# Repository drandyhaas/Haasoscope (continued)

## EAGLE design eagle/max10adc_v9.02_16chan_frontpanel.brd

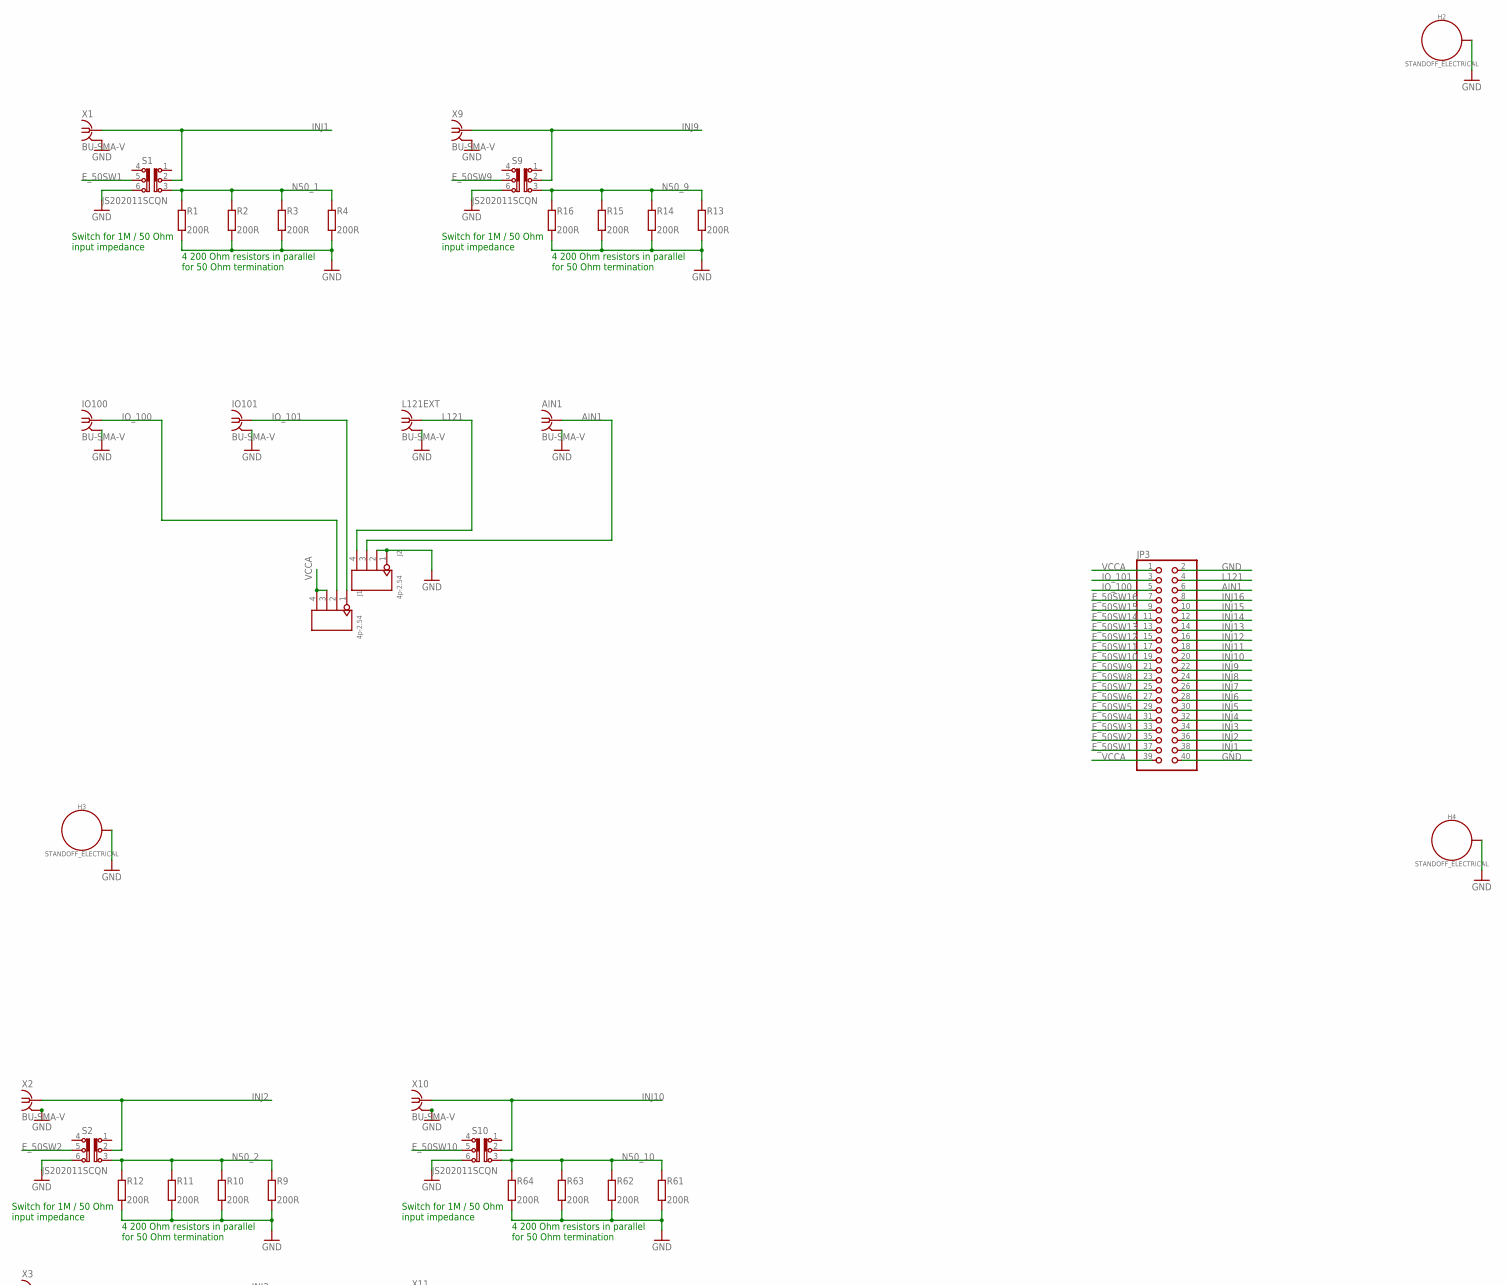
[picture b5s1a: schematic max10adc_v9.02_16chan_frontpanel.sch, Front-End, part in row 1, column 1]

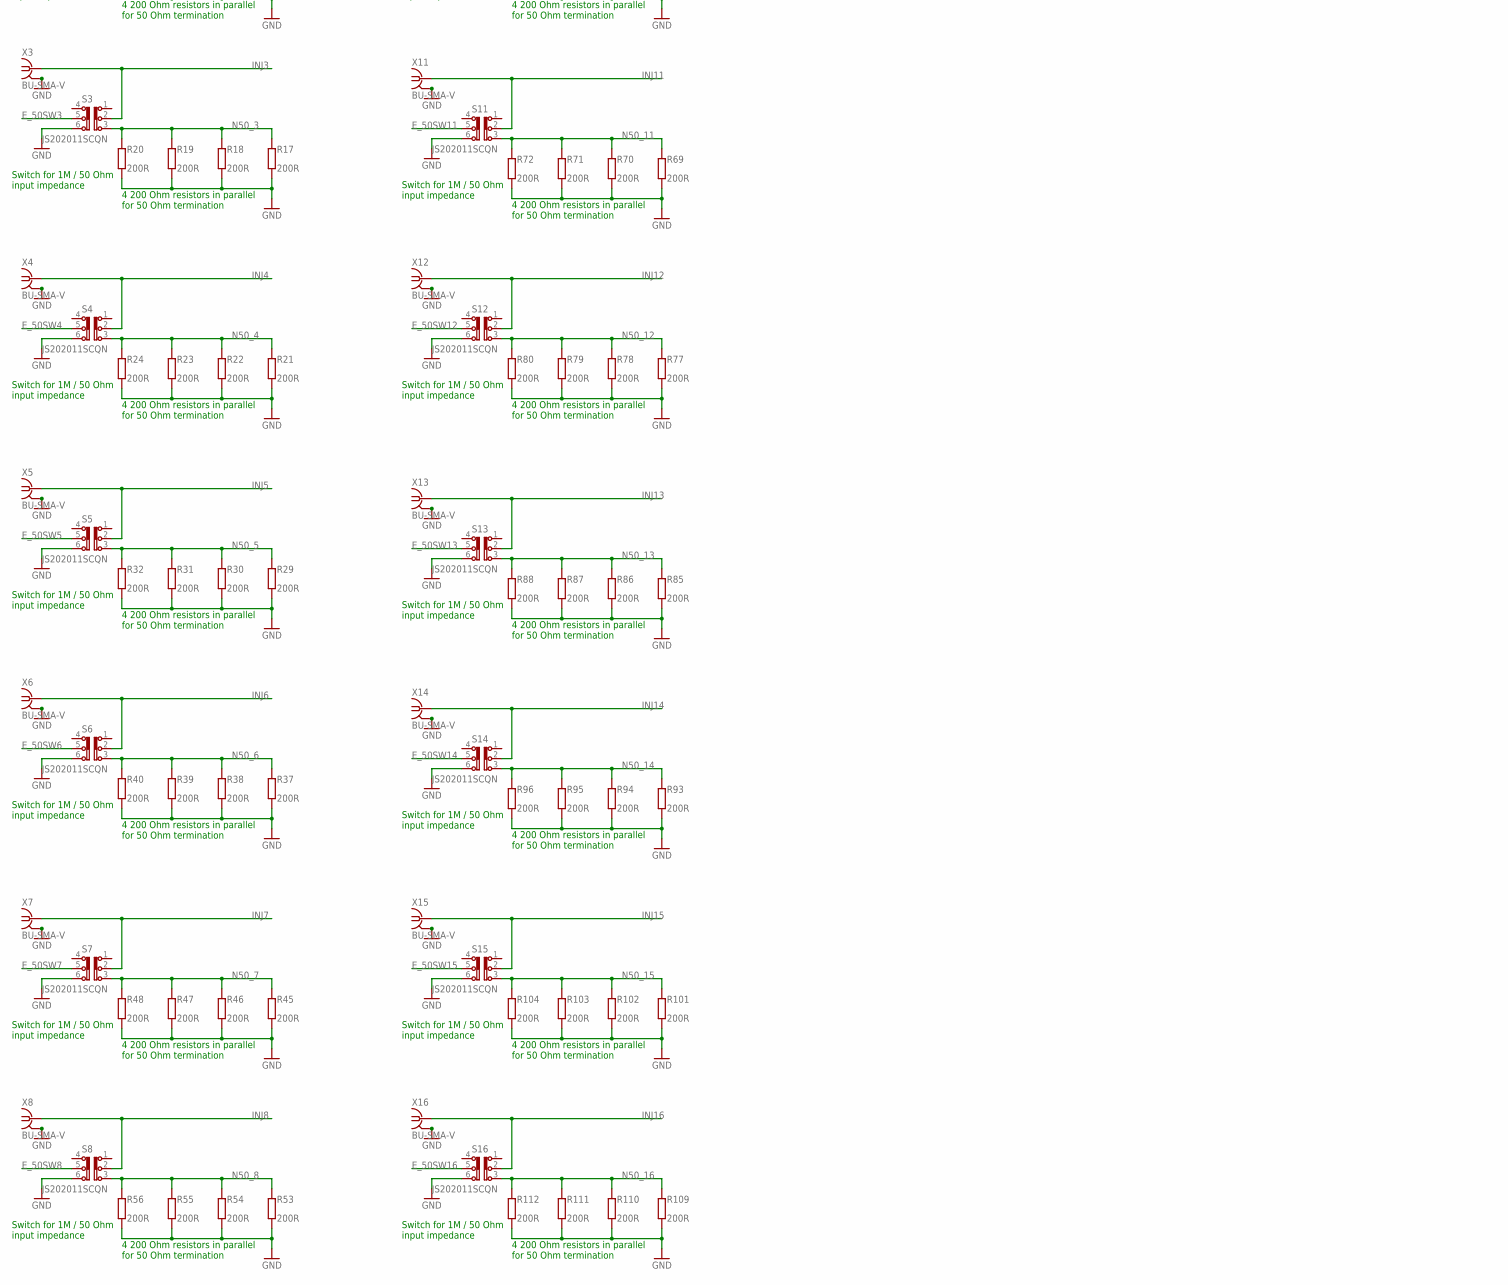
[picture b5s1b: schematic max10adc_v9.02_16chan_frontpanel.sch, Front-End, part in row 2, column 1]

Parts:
AIN1: BU-SMA-V
H2, H3, H4: STANDOFF_ELECTRICAL; STANDOFF-ELECTRICAL
IO100, IO101: BU-SMA-V
J1, J2: 4p-2.54; H4-2.54
JP3: PINHD-2X20; 2X20
L121EXT: BU-SMA-V
R1, R2, R3, R4, R9, R10, R11, R12, R13, R14, R15, R16, R17, R18, R19, R20, R21, R22, R23, R24, R29, R30, R31, R32, R37, R38, R39, R40, R45, R46, R47, R48, R53, R54, R55, R56, R61, R62, R63, R64, R69, R70, R71, R72, R77, R78, R79, R80, R85, R86, R87, R88, R93, R94, R95, R96, R101, R102, R103, R104, R109, R110, R111, R112: 200R; R0805
S1, S2, S3, S4, S5, S6, S7, S8, S9, S10, S11, S12, S13, S14, S15, S16: JS202011SCQN
X1, X2, X3, X4, X5, X6, X7, X8, X9, X10, X11, X12, X13, X14, X15, X16: BU-SMA-V

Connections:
AIN1: AIN1.1, J2.3, JP3.6
E_50SW1: JP3.37, S1.5
E_50SW2: JP3.35, S2.5
E_50SW3: JP3.33, S3.5
E_50SW4: JP3.31, S4.5
E_50SW5: JP3.29, S5.5
E_50SW6: JP3.27, S6.5
E_50SW7: JP3.25, S7.5
E_50SW8: JP3.23, S8.5
E_50SW9: JP3.21, S9.5
E_50SW10: JP3.19, S10.5
E_50SW11: JP3.17, S11.5
E_50SW12: JP3.15, S12.5
E_50SW13: JP3.13, S13.5
E_50SW14: JP3.11, S14.5
E_50SW15: JP3.9, S15.5
E_50SW16: JP3.7, S16.5
GND: AIN1.2, AIN1.3 (2), AIN1.4 (2), AIN1.5 (2), H2.P1, H3.P1, H4.P1, IO100.2, IO100.3 (2), IO100.4 (2), IO100.5 (2), IO101.2, IO101.3 (2), IO101.4 (2), IO101.5 (2), J2.1, J2.2, JP3.2, JP3.40, L121EXT.2, L121EXT.3 (2), L121EXT.4 (2), L121EXT.5 (2), R1.2, R2.2, R3.2, R4.2, R9.2, R10.2, R11.2, R12.2, R13.2, R14.2, R15.2, R16.2, R17.2, R18.2, R19.2, R20.2, R21.2, R22.2, R23.2, R24.2, R29.2, R30.2, R31.2, R32.2, R37.2, R38.2, R39.2, R40.2, R45.2, R46.2, R47.2, R48.2, R53.2, R54.2, R55.2, R56.2, R61.2, R62.2, R63.2, R64.2, R69.2, R70.2, R71.2, R72.2, R77.2, R78.2, R79.2, R80.2, R85.2, R86.2, R87.2, R88.2, R93.2, R94.2, R95.2, R96.2, R101.2, R102.2, R103.2, R104.2, R109.2, R110.2, R111.2, R112.2, S1.6, S2.6, S3.6, S4.6, S5.6, S6.6, S7.6, S8.6, S9.6, S10.6, S11.6, S12.6, S13.6, S14.6, S15.6, S16.6, X1.2, X1.3 (2), X1.4 (2), X1.5 (2), X2.2, X2.3 (2), X2.4 (2), X2.5 (2), X3.2, X3.3 (2), X3.4 (2), X3.5 (2), X4.2, X4.3 (2), X4.4 (2), X4.5 (2), X5.2, X5.3 (2), X5.4 (2), X5.5 (2), X6.2, X6.3 (2), X6.4 (2), X6.5 (2), X7.2, X7.3 (2), X7.4 (2), X7.5 (2), X8.2, X8.3 (2), X8.4 (2), X8.5 (2), X9.2, X9.3 (2), X9.4 (2), X9.5 (2), X10.2, X10.3 (2), X10.4 (2), X10.5 (2), X11.2, X11.3 (2), X11.4 (2), X11.5 (2), X12.2, X12.3 (2), X12.4 (2), X12.5 (2), X13.2, X13.3 (2), X13.4 (2), X13.5 (2), X14.2, X14.3 (2), X14.4 (2), X14.5 (2), X15.2, X15.3 (2), X15.4 (2), X15.5 (2), X16.2, X16.3 (2), X16.4 (2), X16.5 (2)
INJ1: JP3.38, S1.2, X1.1
INJ2: JP3.36, S2.2, X2.1
INJ3: JP3.34, S3.2, X3.1
INJ4: JP3.32, S4.2, X4.1
INJ5: JP3.30, S5.2, X5.1
INJ6: JP3.28, S6.2, X6.1
INJ7: JP3.26, S7.2, X7.1
INJ8: JP3.24, S8.2, X8.1
INJ9: JP3.22, S9.2, X9.1
INJ10: JP3.20, S10.2, X10.1
INJ11: JP3.18, S11.2, X11.1
INJ12: JP3.16, S12.2, X12.1
INJ13: JP3.14, S13.2, X13.1
INJ14: JP3.12, S14.2, X14.1
INJ15: JP3.10, S15.2, X15.1
INJ16: JP3.8, S16.2, X16.1
IO_100: IO100.1, J1.2, JP3.5
IO_101: IO101.1, J1.1, JP3.3
L121: J2.4, JP3.4, L121EXT.1
N50_1: R1.1, R2.1, R3.1, R4.1, S1.3
N50_2: R9.1, R10.1, R11.1, R12.1, S2.3
N50_3: R17.1, R18.1, R19.1, R20.1, S3.3
N50_4: R21.1, R22.1, R23.1, R24.1, S4.3
N50_5: R29.1, R30.1, R31.1, R32.1, S5.3
N50_6: R37.1, R38.1, R39.1, R40.1, S6.3
N50_7: R45.1, R46.1, R47.1, R48.1, S7.3
N50_8: R53.1, R54.1, R55.1, R56.1, S8.3
N50_9: R13.1, R14.1, R15.1, R16.1, S9.3
N50_10: R61.1, R62.1, R63.1, R64.1, S10.3
N50_11: R69.1, R70.1, R71.1, R72.1, S11.3
N50_12: R77.1, R78.1, R79.1, R80.1, S12.3
N50_13: R85.1, R86.1, R87.1, R88.1, S13.3
N50_14: R93.1, R94.1, R95.1, R96.1, S14.3
N50_15: R101.1, R102.1, R103.1, R104.1, S15.3
N50_16: R109.1, R110.1, R111.1, R112.1, S16.3
VCCA: J1.3, J1.4, JP3.1, JP3.39

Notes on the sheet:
4 200 Ohm resistors in parallel for 50 Ohm termination
Switch for 1M / 50 Ohm input impedance

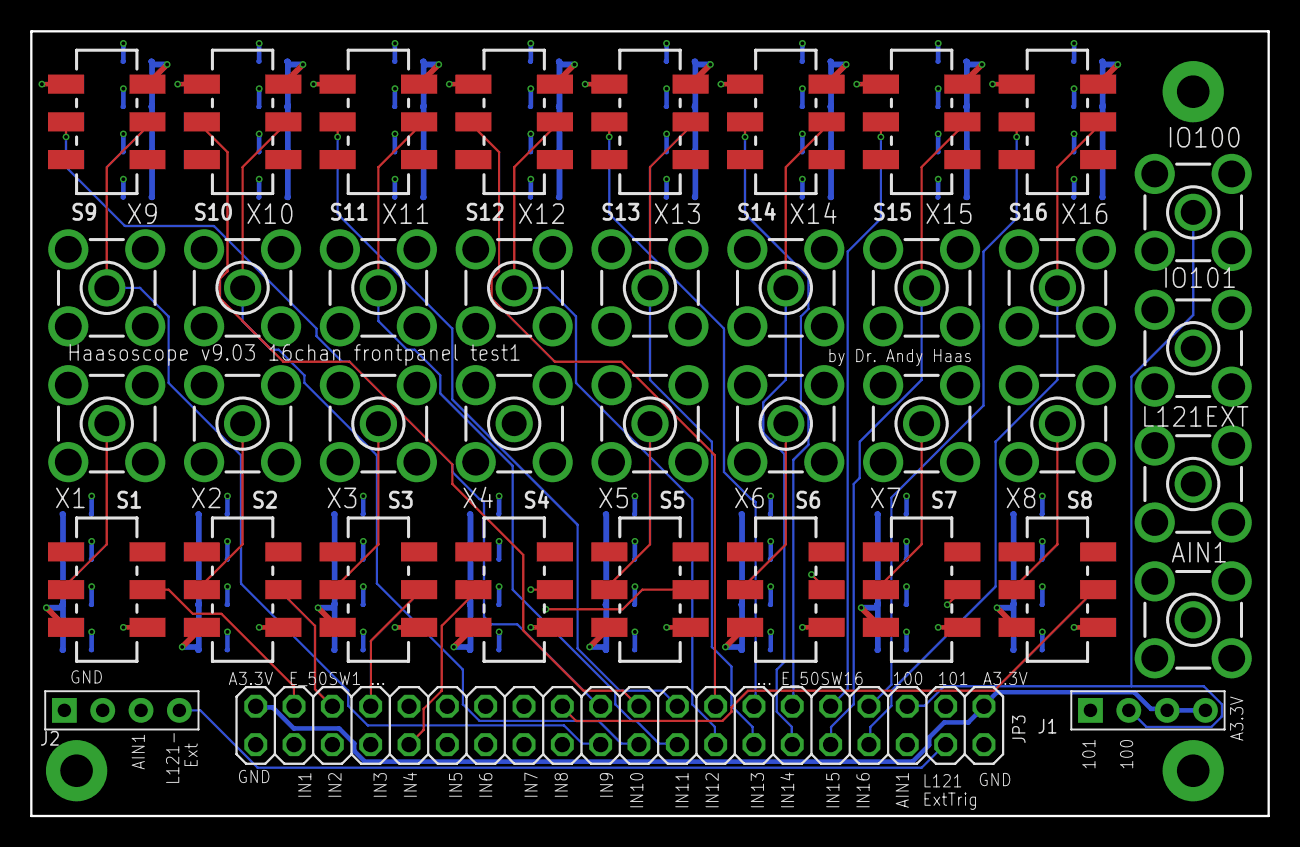
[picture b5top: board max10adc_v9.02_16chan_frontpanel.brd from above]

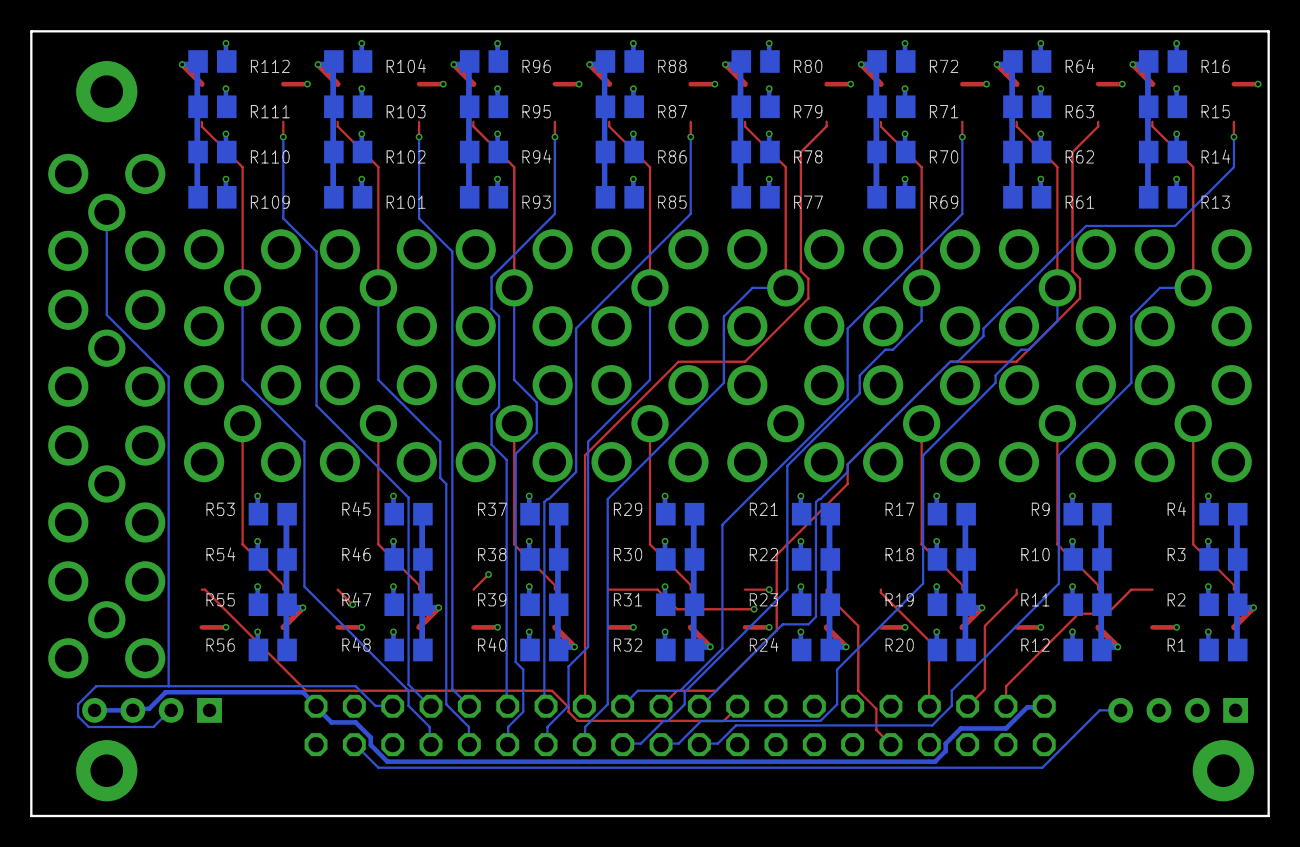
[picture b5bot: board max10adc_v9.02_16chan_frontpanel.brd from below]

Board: 4 copper layers, 82.0 x 52.0 mm, 106 parts (64 on the bottom side), 54 nets.

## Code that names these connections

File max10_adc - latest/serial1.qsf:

# -------------------------------------------------------------------------- #
#
# Copyright (C) 1991-2013 Altera Corporation
# Your use of Altera Corporation's design tools, logic functions 
# and other software and tools, and its AMPP partner logic 
# functions, and any output files from any of the foregoing 
# (including device programming or simulation files), and any 
# associated documentation or information are expressly subject 
# to the terms and conditions of the Altera Program License 
# Subscription Agreement, Altera MegaCore Function License 
# Agreement, or other applicable license agreement, including, 
# without limitation, that your use is for the sole purpose of 
# programming logic devices manufactured by Altera and sold by 
# Altera or its authorized distributors.  Please refer to the 
# applicable agreement for further details.
#
# -------------------------------------------------------------------------- #
#
# Quartus II 32-bit
# Version 13.0.1 Build 232 06/12/2013 Service Pack 1 SJ Web Edition
# Date created = 17:22:48  September 13, 2016
#
# -------------------------------------------------------------------------- #
#
# Notes:
#
# 1) The default values for assignments are stored in the file:
#		serial1_assignment_defaults.qdf
#    If this file doesn't exist, see file:
#		assignment_defaults.qdf
#
# 2) Altera recommends that you do not modify this file. This
#    file is updated automatically by the Quartus II software
#    and any changes you make may be lost or overwritten.
#
# -------------------------------------------------------------------------- #


set_global_assignment -name FAMILY "MAX 10"
set_global_assignment -name DEVICE 10M08SAE144C8GES
set_global_assignment -name TOP_LEVEL_ENTITY serial1
set_global_assignment -name ORIGINAL_QUARTUS_VERSION "13.0 SP1"
set_global_assignment -name PROJECT_CREATION_TIME_DATE "17:22:48  SEPTEMBER 13, 2016"
set_global_assignment -name LAST_QUARTUS_VERSION 15.0.0
set_global_assignment -name PROJECT_OUTPUT_DIRECTORY output_files
set_global_assignment -name MIN_CORE_JUNCTION_TEMP 0
set_global_assignment -name MAX_CORE_JUNCTION_TEMP 85
set_global_assignment -name ERROR_CHECK_FREQUENCY_DIVISOR 2
set_global_assignment -name PARTITION_NETLIST_TYPE SOURCE -section_id Top
set_global_assignment -name PARTITION_FITTER_PRESERVATION_LEVEL PLACEMENT_AND_ROUTING -section_id Top
set_global_assignment -name PARTITION_COLOR 16764057 -section_id Top
set_global_assignment -name STRATIX_DEVICE_IO_STANDARD "3.3-V LVTTL"
set_location_assignment PIN_93 -to 232_in
set_location_assignment PIN_92 -to 232_out
set_location_assignment PIN_33 -to clk_flash_out
set_location_assignment PIN_38 -to din1[7]
set_location_assignment PIN_39 -to din1[6]
set_location_assignment PIN_41 -to din1[5]
set_location_assignment PIN_43 -to din1[4]
set_location_assignment PIN_44 -to din1[3]
set_location_assignment PIN_45 -to din1[2]
set_location_assignment PIN_46 -to din1[1]
set_location_assignment PIN_47 -to din1[0]
set_location_assignment PIN_50 -to din2[7]
set_location_assignment PIN_52 -to din2[6]
set_location_assignment PIN_54 -to din2[5]
set_location_assignment PIN_55 -to din2[4]
set_location_assignment PIN_56 -to din2[3]
set_location_assignment PIN_57 -to din2[2]
set_location_assignment PIN_58 -to din2[1]
set_location_assignment PIN_59 -to din2[0]
set_location_assignment PIN_60 -to din3[7]
set_location_assignment PIN_62 -to din3[6]
set_location_assignment PIN_64 -to din3[5]
set_location_assignment PIN_65 -to din3[4]
set_location_assignment PIN_66 -to din3[3]
set_location_assignment PIN_69 -to din3[2]
set_location_assignment PIN_70 -to din3[1]
set_location_assignment PIN_74 -to din3[0]
set_location_assignment PIN_75 -to din4[7]
set_location_assignment PIN_76 -to din4[6]
set_location_assignment PIN_77 -to din4[5]
set_location_assignment PIN_78 -to din4[4]
set_location_assignment PIN_79 -to din4[3]
set_location_assignment PIN_81 -to din4[2]
set_location_assignment PIN_84 -to din4[1]
set_location_assignment PIN_85 -to din4[0]
set_location_assignment PIN_96 -to 232_out2
set_location_assignment PIN_120 -to led1
set_location_assignment PIN_121 -to led2
set_location_assignment PIN_124 -to led3
set_location_assignment PIN_28 -to outclk_pin
set_location_assignment PIN_86 -to trig_in_towards_left
set_location_assignment PIN_87 -to trig_out_to_right
set_location_assignment PIN_106 -to trig_out_to_left
set_location_assignment PIN_105 -to trig_in_towards_right
set_global_assignment -name PROJECT_IP_REGENERATION_POLICY ALWAYS_REGENERATE_IP
set_global_assignment -name POWER_PRESET_COOLING_SOLUTION "23 MM HEAT SINK WITH 200 LFPM AIRFLOW"
set_global_assignment -name POWER_BOARD_THERMAL_MODEL "NONE (CONSERVATIVE)"
set_global_assignment -name FLOW_ENABLE_POWER_ANALYZER ON
set_global_assignment -name POWER_DEFAULT_INPUT_IO_TOGGLE_RATE "12.5 %"
set_location_assignment PIN_27 -to clock_ext_osc
set_location_assignment PIN_26 -to clock_in
set_location_assignment PIN_131 -to CD
set_location_assignment PIN_140 -to CLKO
set_location_assignment PIN_132 -to CS
set_location_assignment PIN_135 -to DO
set_location_assignment PIN_134 -to RSTO
set_parameter -name SERIAL_BAUD_RATE 1500000
set_parameter -name SERIAL_BAUD_RATE_ARDUINO 9600
set_location_assignment PIN_22 -to outsel_out
set_location_assignment PIN_25 -to format_out
set_location_assignment PIN_24 -to div_out
set_global_assignment -name EDA_SIMULATION_TOOL "ModelSim-Altera (Verilog)"
set_global_assignment -name EDA_TIME_SCALE "1 ps" -section_id eda_simulation
set_global_assignment -name EDA_OUTPUT_DATA_FORMAT "VERILOG HDL" -section_id eda_simulation
set_global_assignment -name EDA_USER_COMPILED_SIMULATION_LIBRARY_DIRECTORY "C:\\haas\\Dropbox\\documents\\FPGA\\QuartusII\\serial_vga_pong_max10_adc\\simulation\\modelsim" -section_id eda_simulation
set_global_assignment -name EDA_GENERATE_FUNCTIONAL_NETLIST ON -section_id eda_simulation
set_location_assignment PIN_110 -to carryin -disable
set_location_assignment PIN_111 -to carryout -disable
set_location_assignment PIN_130 -to ledbase
set_location_assignment PIN_98 -to 232_in2
set_location_assignment PIN_88 -to offset[0]
set_location_assignment PIN_89 -to offset[1]
set_location_assignment PIN_90 -to offset[2]
set_location_assignment PIN_91 -to offset[3]
set_location_assignment PIN_21 -to gainsw[0]
set_location_assignment PIN_29 -to gainsw[1]
set_location_assignment PIN_100 -to gainsw[2]
set_location_assignment PIN_101 -to gainsw[3]
set_parameter -name ADC_RAM_WIDTH 12
set_location_assignment PIN_127 -to led4
set_location_assignment PIN_32 -to clk_flash_out_2
set_global_assignment -name BDF_FILE serial1.bdf
set_global_assignment -name VERILOG_FILE ring_counter.v
set_global_assignment -name VERILOG_FILE tdc2.v
set_global_assignment -name VERILOG_FILE oscillo.v
set_global_assignment -name VERILOG_FILE serialprocessor.v
set_global_assignment -name VERILOG_FILE serialprocessor_slave.v
set_global_assignment -name VHDL_FILE SSD1306.vhd
set_global_assignment -name VHDL_FILE SPI.vhd
set_global_assignment -name VHDL_FILE i2c_master.vhd
set_global_assignment -name VERILOG_FILE async.v
set_global_assignment -name VERILOG_FILE demux1.v
set_global_assignment -name CDF_FILE output_files/Chain1.cdf
set_global_assignment -name CDF_FILE output_files/Chain2.cdf
set_global_assignment -name QIP_FILE mypll2.qip
set_global_assignment -name QIP_FILE ram1.qip
set_global_assignment -name QIP_FILE dpram2.qip
set_global_assignment -name QIP_FILE lp_ram_dp.qip
set_global_assignment -name QIP_FILE myadc/synthesis/myadc.qip
set_location_assignment PIN_118 -to i2c_sda
set_location_assignment PIN_119 -to i2c_scl
set_location_assignment PIN_110 -to usb_dataio[0] -disable
set_location_assignment PIN_111 -to usb_dataio[1] -disable
set_location_assignment PIN_113 -to usb_dataio[2] -disable
set_location_assignment PIN_114 -to usb_dataio[3] -disable
set_location_assignment PIN_118 -to usb_dataio[4] -disable
set_location_assignment PIN_119 -to usb_dataio[5] -disable
set_location_assignment PIN_122 -to usb_dataio[6] -disable
set_location_assignment PIN_132 -to usb_dataio[7] -disable
set_location_assignment PIN_134 -to usb_wr -disable
set_location_assignment PIN_135 -to usb_txe_busy -disable
set_location_assignment PIN_140 -to usb_clk60 -disable
set_instance_assignment -name PARTITION_HIERARCHY root_partition -to | -section_id Top

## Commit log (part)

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2018-10-29 acquire only samplestosend samples, and only signal data ready after all samples have been acquired
2018-10-30 reset highres counter after trigger to prevent glitches
2018-10-30 read the firmware version
2018-10-30 respond with the firmware version to command 147
2018-10-30 change rising edge trigger message to falling
2018-10-31 for no BSOD
2018-11-01 update some parts to TTI
2018-11-02 formatting
2018-11-19 for board v9.0
2018-11-26 remove v8 v9 separate files
2018-11-26 remove v8 stuff
2018-11-26 read v9 switches
2018-11-26 set gain to 1.1 for v9.0 boards
2018-11-27 for 9.01
2018-11-27 for allpcb
2018-12-04 just 6miil distance between drills and traces
2018-12-04 better routing, using just 6mil distance between drills and traces
2018-12-04 150 Ohm inputs for v9.0 boards?
2018-12-07 300 Ohm termination
2018-12-12 removed because not used
2018-12-15 Update README.md
    I've created a 3D model for bottom case. It might come handy also for others.
2018-12-19 case for v8.81
2018-12-22 names on silkscreen
2018-12-22 bottom labels
2019-01-07 v9.01 calib
2019-01-09 minimal serial test
2019-01-10 9.01 calib
2019-01-28 fix crash in printout
2019-01-29 optionally save chan 0 to file
2019-01-30 version 16, dont output clk50 if youre the last one, to reduce noise
2019-02-04 savetofile placement
2019-02-05 check for raspberry pi
2019-02-05 serialdelaytimerwait defaults
2019-02-06 i2c comment
2019-02-16 HW_INIT: Same content, different structure of data
2019-03-21 Show calculated frequency of the signal
2019-03-21 for stacking
2019-03-29 select backend better
2019-04-15 slower on aarch
2019-04-15 linux driver
2019-04-15 linux driver header for rk-3328
2019-04-16 Fixed gaps between base and side walls
2019-05-10 Converted to Python 3.5 but doesn't work.
2019-05-10 Add some debugs.
2019-05-10 theboard forced as int.
2019-05-10 Working version.
2019-05-10 Fix getfirmwareversion function.
2019-05-10 Fix function tellsamplessend.
2019-05-10 Fix function tellbytesskip.
2019-05-10 Fix function telldownsample.
2019-05-10 Fix function settriggertime.
2019-05-10 Fix function tellserialdelaytimerwait.
2019-05-10 Fix function tellSPIsetup.
2019-05-10 Fix function tellrolltrig.
2019-05-10 Fix function settriggerpoint.
2019-05-10 Fix function telllockinnumtoshift.
2019-05-11 Fix function telltickstowait.
2019-05-11 Fix trigger related functions.
    tellminidisplaychan
    settriggerthresh
    settriggerthresh2
    settriggertype
2019-05-11 Fix function writefirmchan.
2019-05-11 Fix function toggleautorearm.
2019-05-11 Fix function getIDs.
2019-05-11 Fix functions setbacktoserialreadout getotherdata.
2019-05-11 Fix functions getmax10adc getdata.
2019-05-11 Fix functions init getswitchdata getchannels.
2019-05-11 Remove init_test.
2019-05-11 Remove trailing spaces.
2019-05-11 Set savetofile to false.
2019-05-11 Add .gitignore for Python.
2019-07-24 show TDC read
2019-11-20 working on 16 chan board
2019-11-22 2.5msps and 12 bit ram for one channel
2019-12-03 for chan 3 12 bit 2.5Msps
2019-12-03 4x less gain and associated compensation, and input 6 pin connector
2019-12-05 with BOM
2019-12-06 MAX11105
2019-12-09 with 24pF fixed caps
2019-12-10 12 bit trigger and highres
2019-12-12 front panel with 50 Ohm termination and SMAs
2019-12-17 back connectors
2019-12-17 no old drawing
2019-12-17 working OK to 0th order
2019-12-17 trigger stuff working
2019-12-18 initial qt gui
2019-12-18 just do new gui in head branch
2019-12-18 more functionality
2019-12-19 select channels and trigging on channels
2019-12-19 more scrolling, keys, etc
2019-12-20 oversampling
2019-12-20 trigger points
2019-12-27 qwheelevent fix?
2019-12-27 record to file in menu
2020-01-06 oops, remove debug message
2020-01-06 xscaling in file
2020-06-10 test for python3
2020-06-10 some fixes
2020-06-12 a few more bugs
2020-07-05 quit when serial fails
2020-09-08 multi board bug fixes
2020-11-04 Initial check-in of Dockerfile to run Haasoscope in a container.
2020-11-10 for xhost
2020-11-10 command line options
2021-04-16 options for serialdelaytimerwait and numboard
2021-04-16 save data for other board channels too
2021-04-16 find usb connections
2021-04-16 for connecting multiple v9 boards
2021-04-16 connecting case
2021-04-19 for python3
2021-04-19 need baud rate for USB2 in python3
2021-04-19 formatting warnings fixes
2021-04-22 150 ohm termination
2021-04-23 ripyl
2021-04-25 prepare to merge version9
2021-04-25 getting ready for trigout instead of analog in
2021-04-25 trigout pins 6 7 8 10 instead of any analog in
2021-04-26 try to support more than 10 boards
2021-04-26 firmware 18, more than 10 boards
2021-04-26 supporting more than 10 boards, requiring firmware 17 or higher
2021-04-27 for more than 10
2021-04-27 trigger recovery test
2021-04-28 send out trigger syncing info to delaycounter
2021-04-29 for sending triggers and clock out
2021-05-01 wait for normal triggers to stop before calibrating trigger bins
2021-05-02 adjustable clock phase, for sending triggers
2021-05-03 store all digital logic analyzer bits from all boards
2021-05-04 talk to trigger board over serial
2021-05-05 be careful to send out test triggers using the same timing as the real triggers
2021-05-05 rename t
2021-05-05 increment clock phase by 3ns after sync loss
2021-05-05 swap spare left and right, send out just one trigger firing
2021-05-06 h5py file writing
2021-05-06 all boards send triggers out to the right when in noselftrig mode
2021-05-06 some minor options
2021-05-08 set seed on trigboard
2021-05-08 prescale integer
2021-05-08 no trigboard by default
2021-05-08 persist
2021-05-08 early persist plot
2021-05-09 persist plot minor
2021-05-09 put back slow adc
2021-05-09 can turn off display of slow adc channels
2021-05-10 make sure we can talk to the trig board
2021-05-12 for prescale on trigboard
2021-05-13 minor, and expect all boards to have a trigger cable connection
2021-05-13 for rolling control of trigboard
2021-05-18 fastusb2
2021-05-18 usb slow working
2021-05-18 basically working
2021-05-19 faster
2021-05-19 exceptions, and no parallel
2021-05-19 few more speedups, now 500 Hz for r12 for b3
2021-05-19 pwrsv line
2021-05-19 handle negative y values, print MB/s
2021-05-20 3U rack compatible
2021-05-21 3U rack backplane
2021-05-21 before routing
2021-05-21 just look for Haasoscope in ftdi name
2021-05-22 add sdc for timing checks
2021-05-22 almost passes timing
2021-05-23 Fix downsample
2021-05-23 Hold timing exception
2021-05-23 comment out the split between usb60 and other clocks in the sdc file, since it caused occasional issues with ch0 readout!
2021-05-24 fixed the glitch in the first sample of ch0, and pass timing, though with a few set_false_paths
2021-05-24 get rid of set_false_paths for dp_ram - we fail timing, but the firmware works
2021-05-25 markers
2021-05-26 working pretty well, but r12 is missing a sample, and first 2 points of ch0 are identical
2021-05-26 working well, but first 2 points of ch0 are identical
2021-05-27 add ram_width 13
2021-05-27 working on timing and ch123 in nsmp mode
2021-05-28 Working for all channels, by padding start of each channel by 1 byte and then accounting for it in software
2021-05-28 Working well on all Nsamples, with readout on all channels aligned to trigger the same as non-usb2
2021-05-28 Don't bother checking for switch changes if we're not drawing
2021-05-28 update IP
2021-05-28 work on timing a little
2021-05-30 count SendCount_fast down to 0, for faster comparison set usb60 clock asynchronous in sdc again passing timing for setup and hold firmware v19
2021-05-30 remove uniqueid false path
2021-05-31 use clk_50 from pll output set input output delays and pass timing and constrain all paths
2021-06-01 nbytes
2021-06-01 working well accounted for rdaddress latency
2021-06-02 better check for fastusb devices
2021-06-02 add ftdi_config.sh
2021-06-02 fix spacing of trigboard
2021-06-02 add 6mm on top and bottom, to fit in sliders
2021-06-02 lower timeouts on fastusb during mapping
2021-06-03 lower timeouts on fastusb during mapping for real, and set max adc read to 32 bytes
2021-06-03 fix averaging
2021-06-03 fix oversampling average and rms for oversampling
2021-06-03 serialdelaytimer for max10adc sending can set slow adc channels on command line
2021-06-07 set output clock to pllin
2021-06-07 flying fast option
2021-06-07 comments on 51-rules
2021-06-08 faster logic analyzer readout
2021-06-08 don't auto rearm in fastusb mode
2021-06-09 reset stuff during firmware read
2021-06-10 mt compatible things
2021-06-10 mt switchable
2021-06-10 mt command line argument and clean up other arguments
2021-06-10 put usb serial on bottom clean up wire stubs
2021-06-10 output clk don't reset
2021-06-13 pylibftdi and pyftdi reading, for non-mt at least
2021-06-13 pyftdi reading with mt
2021-06-13 pyftdi reading with mt and logicanalyzer and do purgebuffer just for ftd2xx, for now
2021-06-13 adjust chunksize for logicanalyzer
2021-06-14 minor, less printouts, etc.
2021-06-14 minor, settings for ftdi etc.
2021-06-14 auto trigboard port
2021-06-14 run trig board at 921600 baud
2021-06-15 remove 2 wire stubs
2021-06-22 specify data types for h5py writing
2021-07-06 add gnd layer on layer 15
2021-07-07 routed v9.10 6layer rack
2021-09-14 add serial decode for UART in Qt
2021-09-15 set ripyl false
2021-09-20 set font size to 11 pixels, and have toggle for allowing same channel coincidence, firmware v21
2021-09-30 fix file status bar message
2021-09-30 example h5py file reading
2021-09-30 save in float32, so time axis has enough precision (and voltage?)
2021-11-23 ignore tty USB2 connections when doing fastusb2
2021-11-23 print error and exit if you try to do fastusb with old firmware
2022-03-02 read out the number of triggers seen, gettrigratecounter
2022-03-03 get trigratecounter every 10s and print to chantext area allow cointime to also be "deadtime" for trigger rate counter
2022-03-07 final touches on trigger rate, firmware 22
2022-03-07 slow paths for trigger counter
2022-05-17 Display trigger threshold
2022-05-26 resend rolling command
2022-05-26 trigger counter every 2s, printouts for rolling trigger
2022-05-26 10 MHz clk on pin 100 (debug4) 1 kHz pulse (SP) on pin 89 (debug1) 50 Hz readout pulse on pin 90 (debug2)
2022-07-06 Initial attempt, need to add duplicate memory buffers
2022-07-20 Initial changes to oscillo.v to include Trigger as an out pin on 106
2022-07-21 averaging machinery in place, works on fastusb2
2022-07-23 100 averages, 1 cycle sort of right, but too much rounding
2022-07-24 Inferred ram avg Down to 2 AVERAGING steps
2022-07-26 Process 4 channels in parallel for averaging
2022-07-27 Write out to USB2 (and not serial)
2022-10-20 Fix QApplication change for python 3.10+
2022-11-05 scripts, env, windows
2022-11-09 __init__ is Python's constructor
2022-12-01 dockerfiles: Fix example dockerfile and provide an example start script
    The existing dockerfile is no longer able to run HaasoscopeQt.py due
    to recent Python 3.11 changes and due to module changes in the
    HaasoscopeQt.py code. Update the docker build rules to account for
    those changes.
    Also, add in a new haasoscope.sh example script with details on how to
    run the container. Update the documentation with a description of
2022-12-02 dockerfiles: Add information on building a container for Quartus software
    Add a dockerfile that can download the Intel Quartus software and
    prepare a container for running it.
    Add example scripts and update the documentation.
2022-12-08 Allow DAC offsets from GUI up to max Fix bug where settings like supergain are read without rolling trigger
2022-12-14 Minor change for csv output
2022-12-28 don't draw old junk if there was a timeout getting data (as often the case with no rolling trigger)
2022-12-28 Make markers the same color as the line
2022-12-28 Only save to file if there was not a timeout (same as for drawing)
2022-12-29 Add for openocd
2022-12-29 openocd files
2023-01-26 set max for ToT box to numsamples
2023-03-24 update to new FT prog
2023-03-24 trig out for ~80ns on pin 101 if noselftrig is false (the default)
2023-04-05 add script ability, and option to not read switch data
2023-05-03 exceptions during usb2 read
2023-06-12 update trigger board with ext trig in, and add old one
2024-02-16 beta version of Zubair fault handling and rebooting
2024-02-24 Make compatible with no ftd2xx drivers again
2024-05-10 before going to CERN for Zubair
2026-06-05 Set AC/DC for ch 3 correctly - found by Claude
2026-06-05 compiled
2026-06-06 Better on mac
